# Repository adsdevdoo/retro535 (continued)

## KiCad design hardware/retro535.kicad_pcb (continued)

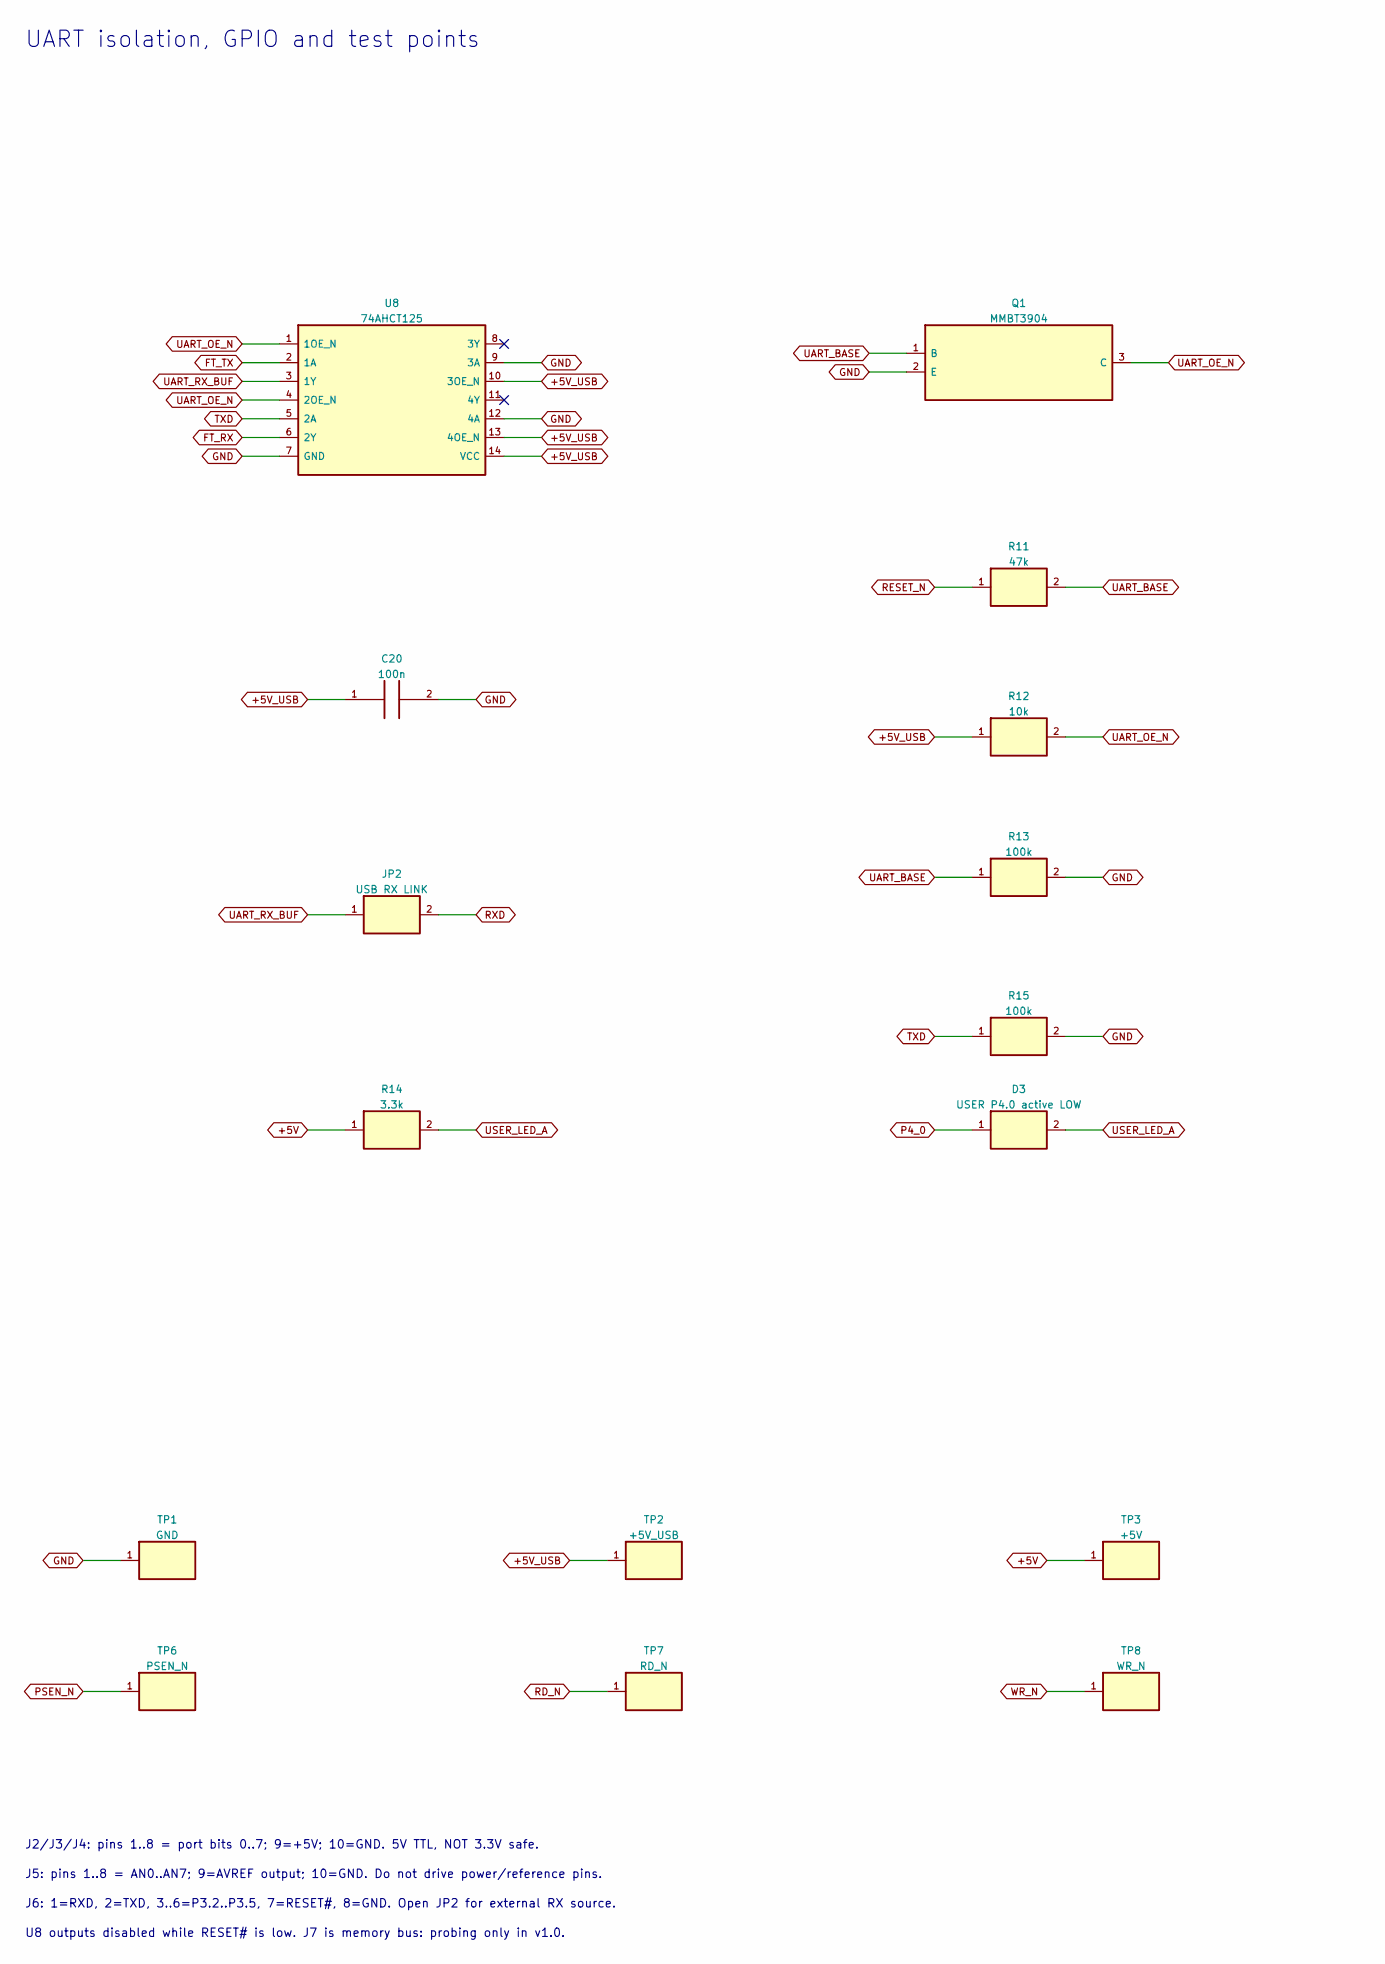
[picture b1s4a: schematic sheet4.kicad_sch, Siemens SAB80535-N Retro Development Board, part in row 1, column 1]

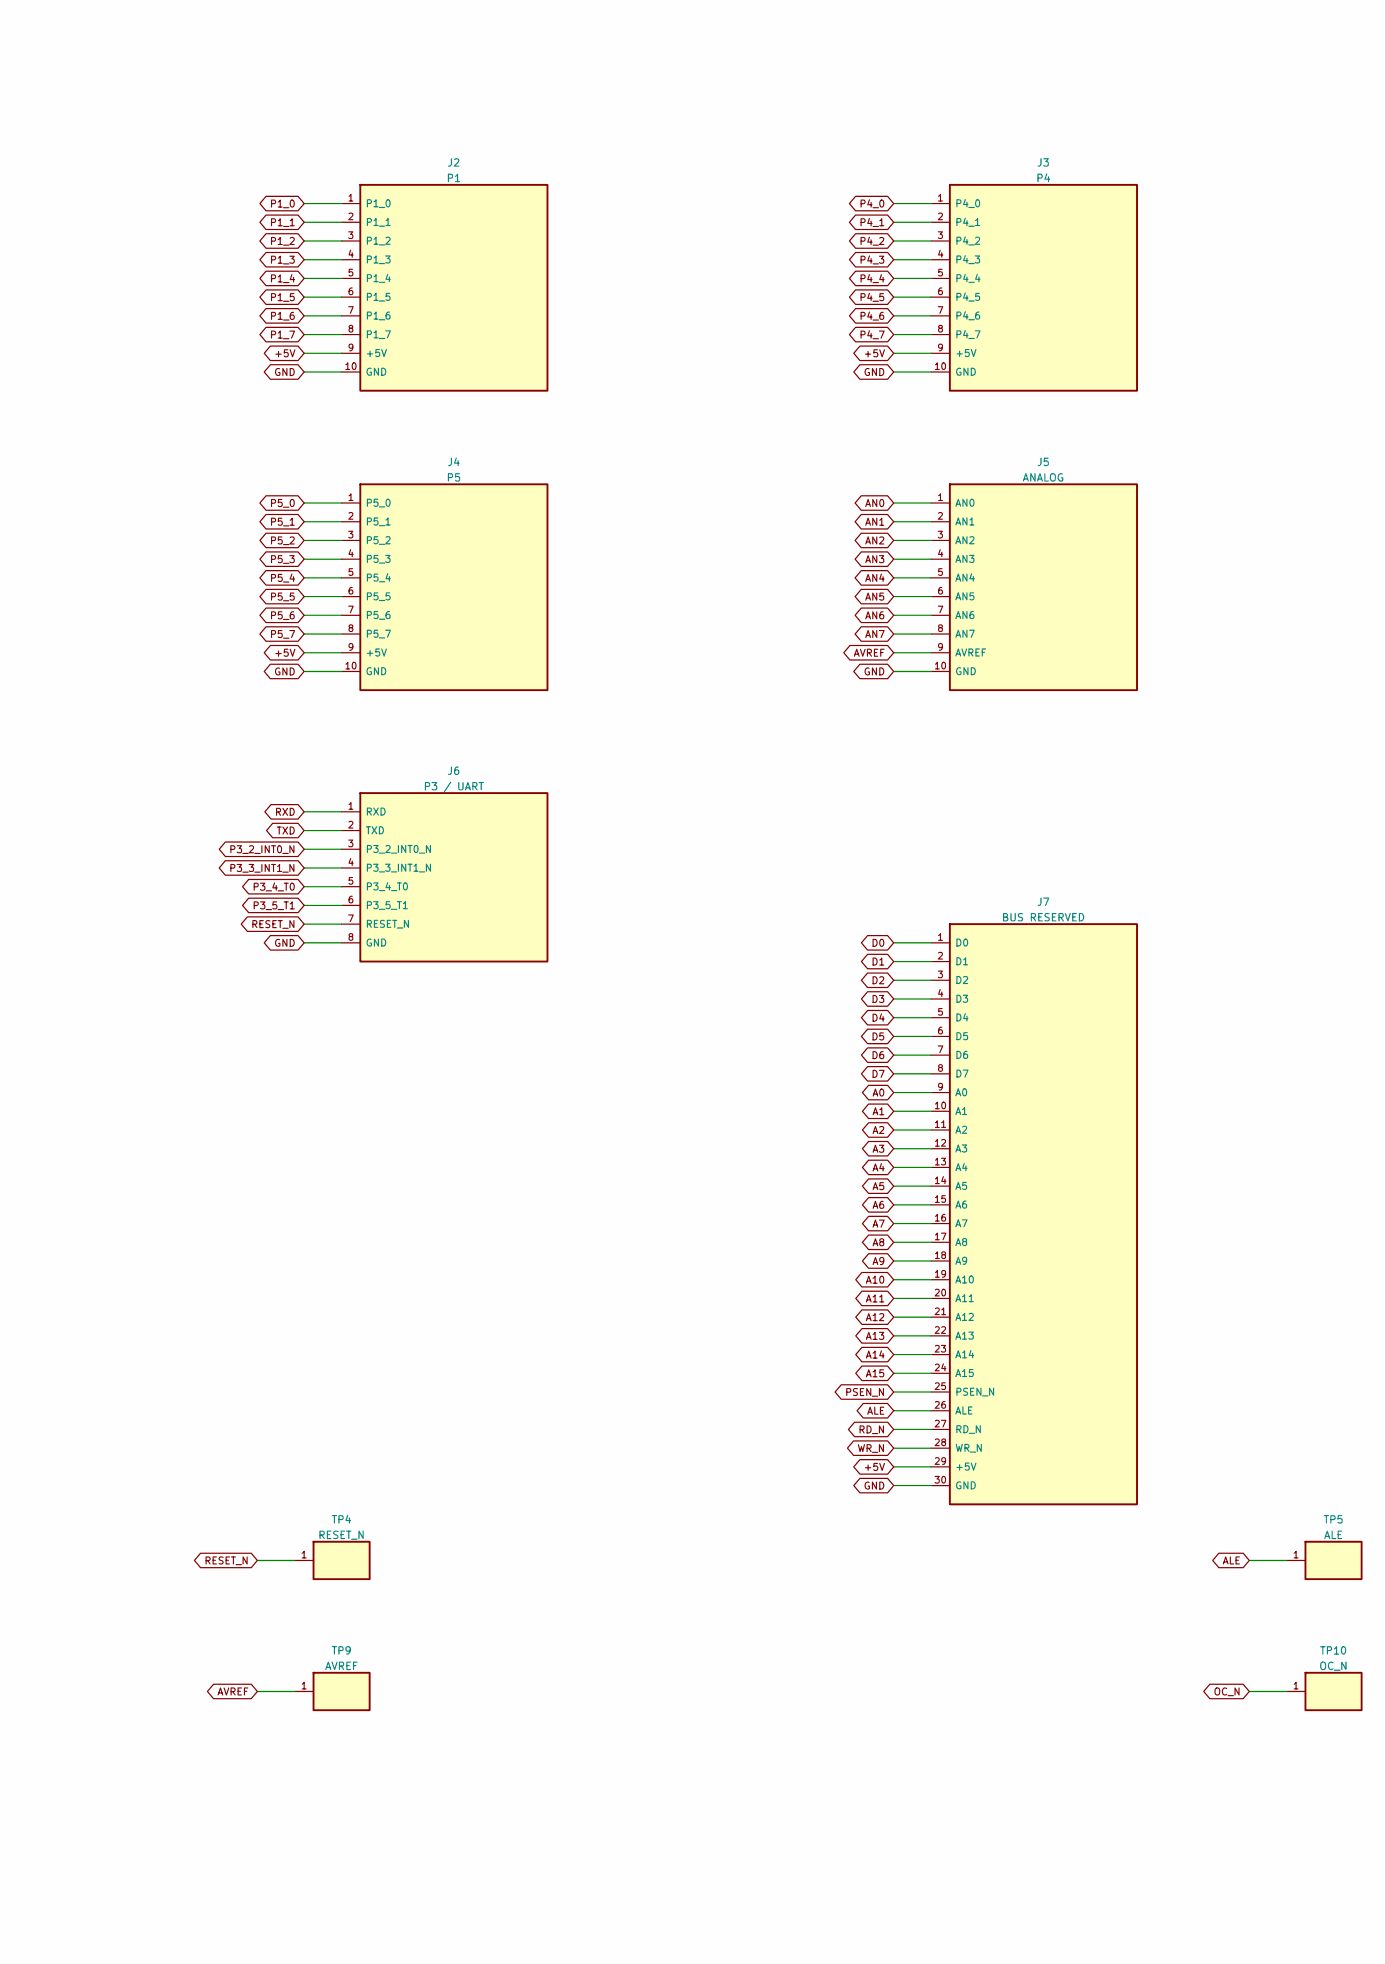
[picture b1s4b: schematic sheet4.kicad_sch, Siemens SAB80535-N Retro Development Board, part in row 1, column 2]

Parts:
C20: 100n; C_0805_2012Metric_Pad1.18x1.45mm_HandSolder; MPN GRM21BR71H104KA01L
D3: USER P4.0 active LOW; LED_0805_2012Metric_Pad1.15x1.40mm_HandSolder; MPN LTST-C170KRKT
J2: P1; PinHeader_2x05_P2.54mm_Vertical; MPN M20-9980546
J3: P4; PinHeader_2x05_P2.54mm_Vertical; MPN M20-9980546
J4: P5; PinHeader_2x05_P2.54mm_Vertical; MPN M20-9980546
J5: ANALOG; PinHeader_2x05_P2.54mm_Vertical; MPN M20-9980546
J6: P3 / UART; PinHeader_2x04_P2.54mm_Vertical; MPN M20-9980446
J7: BUS RESERVED; PinHeader_2x15_P2.54mm_Vertical; MPN M20-9981546
JP2: USB RX LINK; PinHeader_1x02_P2.54mm_Vertical; MPN M20-9990245
Q1: MMBT3904; SOT-23; MPN MMBT3904
R11: 47k; R_0805_2012Metric_Pad1.20x1.40mm_HandSolder; MPN RC0805FR-0747KL
R12: 10k; R_0805_2012Metric_Pad1.20x1.40mm_HandSolder; MPN RC0805FR-0710KL
R13, R15: 100k; R_0805_2012Metric_Pad1.20x1.40mm_HandSolder; MPN RC0805FR-07100KL
R14: 3.3k; R_0805_2012Metric_Pad1.20x1.40mm_HandSolder; MPN RC0805FR-073K3L
TP1: GND; TestPoint_Pad_D2.0mm; MPN PCB test pad
TP2: +5V_USB; TestPoint_Pad_D2.0mm; MPN PCB test pad
TP3: +5V; TestPoint_Pad_D2.0mm; MPN PCB test pad
TP4: RESET_N; TestPoint_Pad_D2.0mm; MPN PCB test pad
TP5: ALE; TestPoint_Pad_D2.0mm; MPN PCB test pad
TP6: PSEN_N; TestPoint_Pad_D2.0mm; MPN PCB test pad
TP7: RD_N; TestPoint_Pad_D2.0mm; MPN PCB test pad
TP8: WR_N; TestPoint_Pad_D2.0mm; MPN PCB test pad
TP9: AVREF; TestPoint_Pad_D2.0mm; MPN PCB test pad
TP10: OC_N; TestPoint_Pad_D2.0mm; MPN PCB test pad
U8: 74AHCT125; SOIC-14_3.9x8.7mm_P1.27mm; MPN SN74AHCT125DR

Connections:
+5V: J2.9 (+5V), J3.9 (+5V), J4.9 (+5V), J7.29 (+5V), R14.1, TP3.1; also elsewhere on the board
+5V_USB: C20.1, R12.1, TP2.1, U8.10 (3OE_N), U8.13 (4OE_N), U8.14 (VCC); also elsewhere on the board
A0: J7.9 (A0); also elsewhere on the board
A1: J7.10 (A1); also elsewhere on the board
A2: J7.11 (A2); also elsewhere on the board
A3: J7.12 (A3); also elsewhere on the board
A4: J7.13 (A4); also elsewhere on the board
A5: J7.14 (A5); also elsewhere on the board
A6: J7.15 (A6); also elsewhere on the board
A7: J7.16 (A7); also elsewhere on the board
A8: J7.17 (A8); also elsewhere on the board
A9: J7.18 (A9); also elsewhere on the board
A10: J7.19 (A10); also elsewhere on the board
A11: J7.20 (A11); also elsewhere on the board
A12: J7.21 (A12); also elsewhere on the board
A13: J7.22 (A13); also elsewhere on the board
A14: J7.23 (A14); also elsewhere on the board
A15: J7.24 (A15); also elsewhere on the board
ALE: J7.26 (ALE), TP5.1; also elsewhere on the board
AN0: J5.1 (AN0); also elsewhere on the board
AN1: J5.2 (AN1); also elsewhere on the board
AN2: J5.3 (AN2); also elsewhere on the board
AN3: J5.4 (AN3); also elsewhere on the board
AN4: J5.5 (AN4); also elsewhere on the board
AN5: J5.6 (AN5); also elsewhere on the board
AN6: J5.7 (AN6); also elsewhere on the board
AN7: J5.8 (AN7); also elsewhere on the board
AVREF: J5.9 (AVREF), TP9.1; also elsewhere on the board
D0: J7.1 (D0); also elsewhere on the board
D1: J7.2 (D1); also elsewhere on the board
D2: J7.3 (D2); also elsewhere on the board
D3: J7.4 (D3); also elsewhere on the board
D4: J7.5 (D4); also elsewhere on the board
D5: J7.6 (D5); also elsewhere on the board
D6: J7.7 (D6); also elsewhere on the board
D7: J7.8 (D7); also elsewhere on the board
FT_RX: U8.6 (2Y); also elsewhere on the board
FT_TX: U8.2 (1A); also elsewhere on the board
GND: C20.2, J2.10 (GND), J3.10 (GND), J4.10 (GND), J5.10 (GND), J6.8 (GND), J7.30 (GND), Q1.2 (E), R13.2, R15.2, TP1.1, U8.7 (GND), U8.9 (3A), U8.12 (4A); also elsewhere on the board
OC_N: TP10.1; also elsewhere on the board
P1_0: J2.1 (P1_0); also elsewhere on the board
P1_1: J2.2 (P1_1); also elsewhere on the board
P1_2: J2.3 (P1_2); also elsewhere on the board
P1_3: J2.4 (P1_3); also elsewhere on the board
P1_4: J2.5 (P1_4); also elsewhere on the board
P1_5: J2.6 (P1_5); also elsewhere on the board
P1_6: J2.7 (P1_6); also elsewhere on the board
P1_7: J2.8 (P1_7); also elsewhere on the board
P3_2_INT0_N: J6.3 (P3_2_INT0_N); also elsewhere on the board
P3_3_INT1_N: J6.4 (P3_3_INT1_N); also elsewhere on the board
P3_4_T0: J6.5 (P3_4_T0); also elsewhere on the board
P3_5_T1: J6.6 (P3_5_T1); also elsewhere on the board
P4_0: D3.1, J3.1 (P4_0); also elsewhere on the board
P4_1: J3.2 (P4_1); also elsewhere on the board
P4_2: J3.3 (P4_2); also elsewhere on the board
P4_3: J3.4 (P4_3); also elsewhere on the board
P4_4: J3.5 (P4_4); also elsewhere on the board
P4_5: J3.6 (P4_5); also elsewhere on the board
P4_6: J3.7 (P4_6); also elsewhere on the board
P4_7: J3.8 (P4_7); also elsewhere on the board
P5_0: J4.1 (P5_0); also elsewhere on the board
P5_1: J4.2 (P5_1); also elsewhere on the board
P5_2: J4.3 (P5_2); also elsewhere on the board
P5_3: J4.4 (P5_3); also elsewhere on the board
P5_4: J4.5 (P5_4); also elsewhere on the board
P5_5: J4.6 (P5_5); also elsewhere on the board
P5_6: J4.7 (P5_6); also elsewhere on the board
P5_7: J4.8 (P5_7); also elsewhere on the board
PSEN_N: J7.25 (PSEN_N), TP6.1; also elsewhere on the board
RD_N: J7.27 (RD_N), TP7.1; also elsewhere on the board
RESET_N: J6.7 (RESET_N), R11.1, TP4.1; also elsewhere on the board
RXD: J6.1 (RXD), JP2.2; also elsewhere on the board
TXD: J6.2 (TXD), R15.1, U8.5 (2A); also elsewhere on the board
UART_BASE: Q1.1 (B), R11.2, R13.1
UART_OE_N: Q1.3 (C), R12.2, U8.1 (1OE_N), U8.4 (2OE_N)
UART_RX_BUF: JP2.1, U8.3 (1Y)
USER_LED_A: D3.2, R14.2
WR_N: J7.28 (WR_N), TP8.1; also elsewhere on the board

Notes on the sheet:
UART isolation, GPIO and test points
J2/J3/J4: pins 1..8 = port bits 0..7; 9=+5V; 10=GND. 5V TTL, NOT 3.3V safe.
J5: pins 1..8 = AN0..AN7; 9=AVREF output; 10=GND. Do not drive power/reference pins.
J6: 1=RXD, 2=TXD, 3..6=P3.2..P3.5, 7=RESET#, 8=GND. Open JP2 for external RX source.
U8 outputs disabled while RESET# is low. J7 is memory bus: probing only in v1.0.

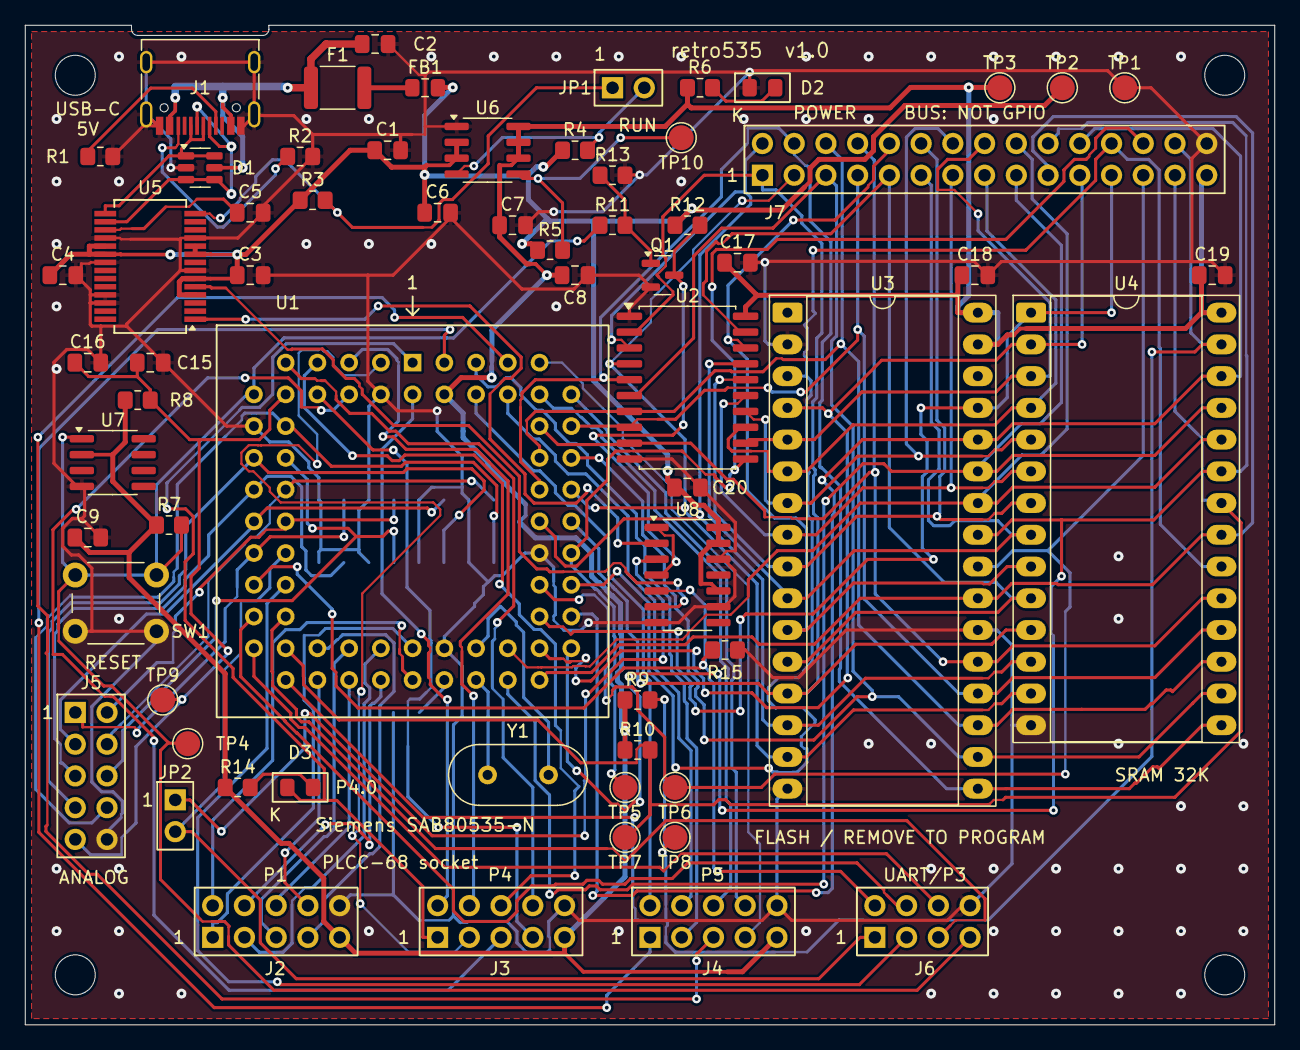
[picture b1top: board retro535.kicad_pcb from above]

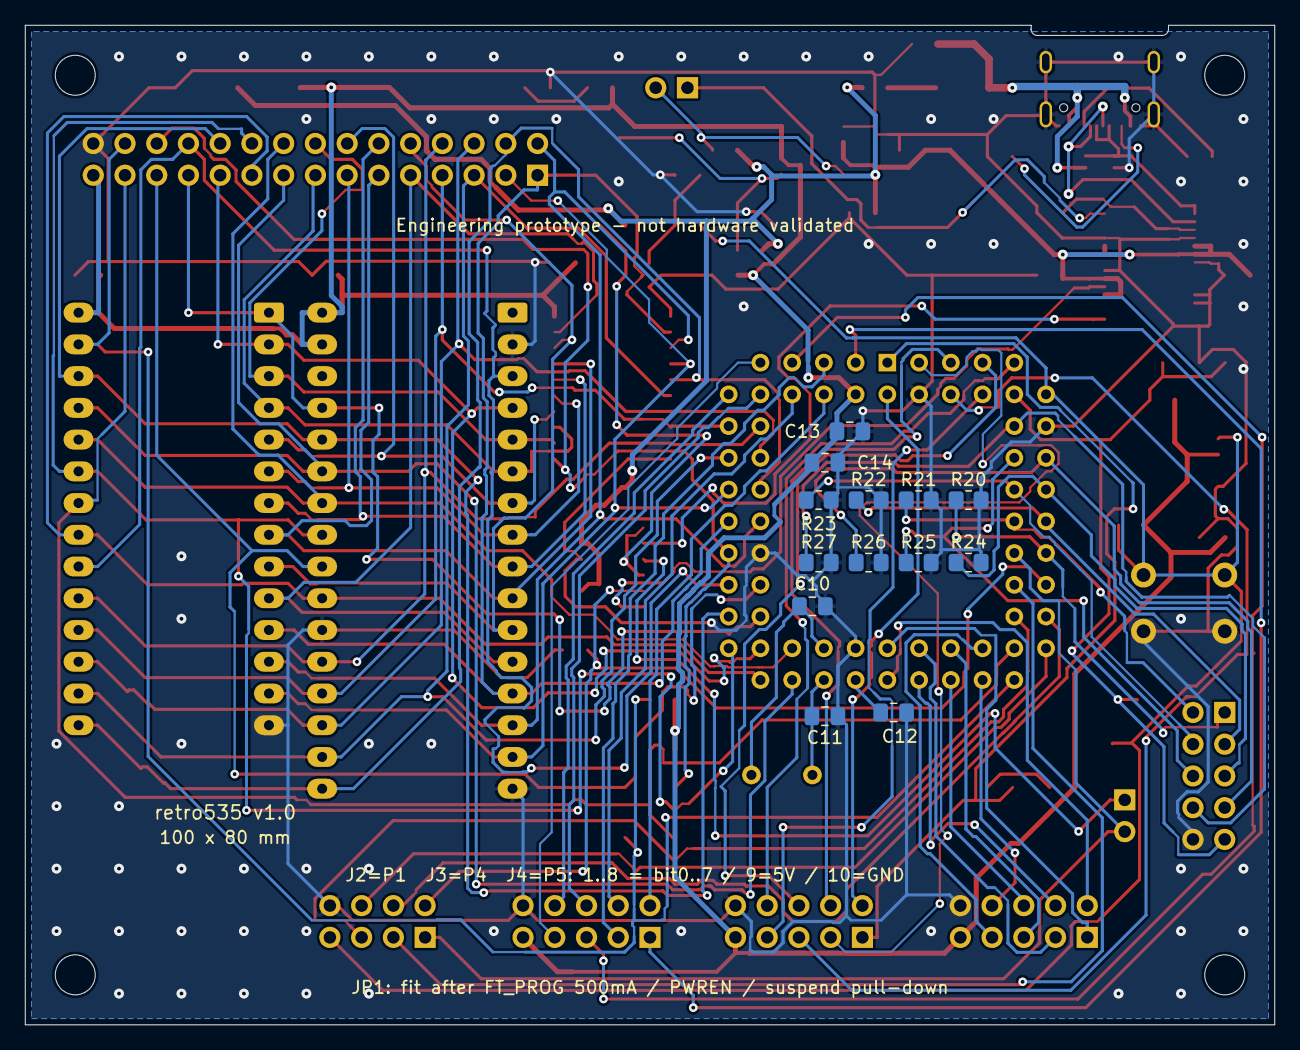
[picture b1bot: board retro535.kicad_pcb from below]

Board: 2 copper layers, 100.0 x 80.0 mm, 82 parts (13 on the bottom side), 91 nets.

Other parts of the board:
H1, H2, H3, H4: M3 NPTH; MountingHole_3.2mm_M3

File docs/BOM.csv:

Reference,Qty,Value,MPN,Footprint,Datasheet,Notes
U1,1,SAB80535-N,SAB80535-N,Retro535:PLCC68_PreciDip_540-99-068-24-000-1,https://www.ardent-tool.com/datasheets/Siemens_SAB80515_80535.pdf,Supplied by user; socket listed separately
U2,1,74HCT573,SN74HCT573DWR,Retro535:SOIC-20W_7.5x12.8mm_P1.27mm,https://www.ti.com/lit/ds/symlink/sn74hct573.pdf,
U3,1,SST39SF010A-70-4C-PHE,SST39SF010A-70-4C-PHE,Retro535:DIP-32_W15.24mm_Socket_LongPads,https://ww1.microchip.com/downloads/aemDocuments/documents/M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,
U4,1,AS6C62256A-70PCN,AS6C62256A-70PCN,Retro535:DIP-28_W15.24mm_Socket_LongPads,https://www.alliancememory.com/wp-content/uploads/AS6C62256A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,EOL; no substitution without level review
J1,1,USB-C,TYPE-C-31-M-12,Retro535:USB_C_Receptacle_HRO_TYPE-C-31-M-12,https://datasheet.lcsc.com/datasheet/pdf/9e56b777c022540fcce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,
R1,1,5.1k,RC0805FR-075K1L,Retro535:R_0805_2012Metric_Pad1.20x1.40mm_HandSolder,,
R2,1,5.1k,RC0805FR-075K1L,Retro535:R_0805_2012Metric_Pad1.20x1.40mm_HandSolder,,
F1,1,0.75A PTC,MF-MSMF075-2,Retro535:Fuse_1812_4532Metric,,
FB1,1,600R@100MHz,BLM21PG601SN1D,Retro535:L_0805_2012Metric_Pad1.15x1.40mm_HandSolder,,
C1,1,4.7u,GRM21BR61C475KA73L,Retro535:C_0805_2012Metric_Pad1.18x1.45mm_HandSolder,,
C2,1,100n,GRM21BR71H104KA01L,Retro535:C_0805_2012Metric_Pad1.18x1.45mm_HandSolder,,
D1,1,USBLC6-2SC6,USBLC6-2SC6,Retro535:SOT-23-6,https://www.st.com/resource/en/datasheet/usblc6-2.pdf,
U5,1,FT232RL,FT232RL,Retro535:SSOP-28_5.3x10.2mm_P0.65mm,https://ftdichip.cn/Support/Documents/DataSheets/ICs/DS_FT232R.pdf,
C3,1,100n,GRM21BR71H104KA01L,Retro535:C_0805_2012Metric_Pad1.18x1.45mm_HandSolder,,
C4,1,100n,GRM21BR71H104KA01L,Retro535:C_0805_2012Metric_Pad1.18x1.45mm_HandSolder,,
C5,1,100n,GRM21BR71H104KA01L,Retro535:C_0805_2012Metric_Pad1.18x1.45mm_HandSolder,,
U6,1,TPS2041BDR,TPS2041BDR,Retro535:SOIC-8_3.9x4.9mm_P1.27mm,https://www.ti.com/lit/ds/symlink/tps2041b.pdf,
R3,1,10k,RC0805FR-0710KL,Retro535:R_0805_2012Metric_Pad1.20x1.40mm_HandSolder,,
R4,1,10k,RC0805FR-0710KL,Retro535:R_0805_2012Metric_Pad1.20x1.40mm_HandSolder,,
JP1,1,RUN - FIT AFTER FT_PROG,M20-9990245,Retro535:PinHeader_1x02_P2.54mm_Vertical,,Fit only after USB provisioning
R5,1,10k,RC0805FR-0710KL,Retro535:R_0805_2012Metric_Pad1.20x1.40mm_HandSolder,,
C6,1,100n,GRM21BR71H104KA01L,Retro535:C_0805_2012Metric_Pad1.18x1.45mm_HandSolder,,
C7,1,4.7u,GRM21BR61C475KA73L,Retro535:C_0805_2012Metric_Pad1.18x1.45mm_HandSolder,,
C8,1,100n,GRM21BR71H104KA01L,Retro535:C_0805_2012Metric_Pad1.18x1.45mm_HandSolder,,
R6,1,2.2k,RC0805FR-072K2L,Retro535:R_0805_2012Metric_Pad1.20x1.40mm_HandSolder,,
D2,1,POWER green,LTST-C170KGKT,Retro535:LED_0805_2012Metric_Pad1.15x1.40mm_HandSolder,,
U7,1,MCP120-475I/SN,MCP120-475I/SN,Retro535:SOIC-8_3.9x4.9mm_P1.27mm,https://ww1.microchip.com/downloads/en/DeviceDoc/11184D.pdf,
R7,1,10k,RC0805FR-0710KL,Retro535:R_0805_2012Metric_Pad1.20x1.40mm_HandSolder,,
SW1,1,RESET,B3F-1000,Retro535:SW_PUSH_6mm,,
C9,1,100n,GRM21BR71H104KA01L,Retro535:C_0805_2012Metric_Pad1.18x1.45mm_HandSolder,,
Y1,1,11.0592MHz CL20p,ECS-110.5-20-4X,Retro535:Crystal_HC49-U_Vertical,https://www.ecsxtal.com/store/pdf/hc-49usx.pdf,
C10,1,30p,GRM2165C1H300JA01D,Retro535:C_0805_2012Metric_Pad1.18x1.45mm_HandSolder,,
C11,1,30p,GRM2165C1H300JA01D,Retro535:C_0805_2012Metric_Pad1.18x1.45mm_HandSolder,,
C12,1,100n,GRM21BR71H104KA01L,Retro535:C_0805_2012Metric_Pad1.18x1.45mm_HandSolder,,
C13,1,100n,GRM21BR71H104KA01L,Retro535:C_0805_2012Metric_Pad1.18x1.45mm_HandSolder,,
C14,1,1u,GRM21BR71C105KA01L,Retro535:C_0805_2012Metric_Pad1.18x1.45mm_HandSolder,,
R8,1,10,RC0805FR-0710RL,Retro535:R_0805_2012Metric_Pad1.20x1.40mm_HandSolder,,
C15,1,100n,GRM21BR71H104KA01L,Retro535:C_0805_2012Metric_Pad1.18x1.45mm_HandSolder,,
C16,1,1u,GRM21BR71C105KA01L,Retro535:C_0805_2012Metric_Pad1.18x1.45mm_HandSolder,,
R20,1,100k,RC0805FR-07100KL,Retro535:R_0805_2012Metric_Pad1.20x1.40mm_HandSolder,,
R21,1,100k,RC0805FR-07100KL,Retro535:R_0805_2012Metric_Pad1.20x1.40mm_HandSolder,,
R22,1,100k,RC0805FR-07100KL,Retro535:R_0805_2012Metric_Pad1.20x1.40mm_HandSolder,,
R23,1,100k,RC0805FR-07100KL,Retro535:R_0805_2012Metric_Pad1.20x1.40mm_HandSolder,,
R24,1,100k,RC0805FR-07100KL,Retro535:R_0805_2012Metric_Pad1.20x1.40mm_HandSolder,,
R25,1,100k,RC0805FR-07100KL,Retro535:R_0805_2012Metric_Pad1.20x1.40mm_HandSolder,,
R26,1,100k,RC0805FR-07100KL,Retro535:R_0805_2012Metric_Pad1.20x1.40mm_HandSolder,,
R27,1,100k,RC0805FR-07100KL,Retro535:R_0805_2012Metric_Pad1.20x1.40mm_HandSolder,,
C17,1,100n,GRM21BR71H104KA01L,Retro535:C_0805_2012Metric_Pad1.18x1.45mm_HandSolder,,
C18,1,100n,GRM21BR71H104KA01L,Retro535:C_0805_2012Metric_Pad1.18x1.45mm_HandSolder,,
C19,1,100n,GRM21BR71H104KA01L,Retro535:C_0805_2012Metric_Pad1.18x1.45mm_HandSolder,,
R9,1,10k,RC0805FR-0710KL,Retro535:R_0805_2012Metric_Pad1.20x1.40mm_HandSolder,,
R10,1,10k,RC0805FR-0710KL,Retro535:R_0805_2012Metric_Pad1.20x1.40mm_HandSolder,,
U8,1,74AHCT125,SN74AHCT125DR,Retro535:SOIC-14_3.9x8.7mm_P1.27mm,https://www.ti.com/lit/ds/symlink/sn74ahct125.pdf,
Q1,1,MMBT3904,MMBT3904,Retro535:SOT-23,,
R11,1,47k,RC0805FR-0747KL,Retro535:R_0805_2012Metric_Pad1.20x1.40mm_HandSolder,,
R12,1,10k,RC0805FR-0710KL,Retro535:R_0805_2012Metric_Pad1.20x1.40mm_HandSolder,,
R13,1,100k,RC0805FR-07100KL,Retro535:R_0805_2012Metric_Pad1.20x1.40mm_HandSolder,,
C20,1,100n,GRM21BR71H104KA01L,Retro535:C_0805_2012Metric_Pad1.18x1.45mm_HandSolder,,
R15,1,100k,RC0805FR-07100KL,Retro535:R_0805_2012Metric_Pad1.20x1.40mm_HandSolder,,
JP2,1,USB RX LINK,M20-9990245,Retro535:PinHeader_1x02_P2.54mm_Vertical,,
R14,1,3.3k,RC0805FR-073K3L,Retro535:R_0805_2012Metric_Pad1.20x1.40mm_HandSolder,,
D3,1,USER P4.0 active LOW,LTST-C170KRKT,Retro535:LED_0805_2012Metric_Pad1.15x1.40mm_HandSolder,,
J2,1,P1,M20-9980546,Retro535:PinHeader_2x05_P2.54mm_Vertical,,
J3,1,P4,M20-9980546,Retro535:PinHeader_2x05_P2.54mm_Vertical,,
J4,1,P5,M20-9980546,Retro535:PinHeader_2x05_P2.54mm_Vertical,,
J5,1,ANALOG,M20-9980546,Retro535:PinHeader_2x05_P2.54mm_Vertical,,
J6,1,P3 / UART,M20-9980446,Retro535:PinHeader_2x04_P2.54mm_Vertical,,
J7,1,BUS RESERVED,M20-9981546,Retro535:PinHeader_2x15_P2.54mm_Vertical,,
TP1,1,GND,PCB test pad,Retro535:TestPoint_Pad_D2.0mm,,
TP2,1,+5V_USB,PCB test pad,Retro535:TestPoint_Pad_D2.0mm,,
TP3,1,+5V,PCB test pad,Retro535:TestPoint_Pad_D2.0mm,,
TP4,1,RESET_N,PCB test pad,Retro535:TestPoint_Pad_D2.0mm,,
TP5,1,ALE,PCB test pad,Retro535:TestPoint_Pad_D2.0mm,,
TP6,1,PSEN_N,PCB test pad,Retro535:TestPoint_Pad_D2.0mm,,
TP7,1,RD_N,PCB test pad,Retro535:TestPoint_Pad_D2.0mm,,
TP8,1,WR_N,PCB test pad,Retro535:TestPoint_Pad_D2.0mm,,
TP9,1,AVREF,PCB test pad,Retro535:TestPoint_Pad_D2.0mm,,
TP10,1,OC_N,PCB test pad,Retro535:TestPoint_Pad_D2.0mm,,
U1 socket,1,PLCC-68 THT,540-99-068-24-000-1,Retro535:PLCC68_PreciDip_540-99-068-24-000-1,https://static.chipdip.ru/lib/825/DOC031825282.pdf,"Preci-Dip, catalogue p94"
U3 socket,1,DIP32 600mil,110-93-632-41-001000,included with U3,,Mill-Max; 2.54mm pitch
U4 socket,1,DIP28 600mil,110-93-628-41-001000,included with U4,,Mill-Max; 2.54mm pitch
JP1/JP2 shunts,2,2.54mm shunt,QPC02SXGN-RC,n/a,,Sullins; fit JP1 only after FT_PROG provisioning

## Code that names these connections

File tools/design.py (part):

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add('U6','TPS2041BDR',SO8,power,(37,10),(265,87),1,source='https://www.ti.com/lit/ds/symlink/tps2041b.pdf')
res('R3','10k','+5V_USB','PWREN_N',(25,17),(330,68))
res('R4','10k','+5V_USB','EN_N',(44,10),(330,84))
two('JP1','RUN - FIT AFTER FT_PROG','Connector_PinHeader_2.54mm:PinHeader_1x02_P2.54mm_Vertical','PWREN_N','EN_N',(47,5),(330,110),1,'M20-9990245',kind='jumper',angle=90)
res('R5','10k','+5V_USB','OC_N',(44,16),(330,132))
cap('C6','100n','+5V_USB',(33,15),(300,165))
cap('C7','4.7u','+5V',(39,16),(365,165))
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res('R13','100k','UART_BASE','GND',(27,32),(155,130),4)
cap('C20','100n','+5V_USB',(29,18),(70,105),4)
res('R15','100k','TXD','GND',(56,50),(155,151),4)
two('JP2','USB RX LINK','Connector_PinHeader_2.54mm:PinHeader_1x02_P2.54mm_Vertical','UART_RX_BUF','RXD',(22,36),(70,135),4,'M20-9990245',kind='jumper')
res('R14','3.3k','+5V','USER_LED_A',(17,61),(70,164),4)
two('D3','USER P4.0 active LOW','LED_SMD:LED_0805_2012Metric_Pad1.15x1.40mm_HandSolder','P4_0','USER_LED_A',(22,61),(155,164),4,'LTST-C170KRKT',kind='led')

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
